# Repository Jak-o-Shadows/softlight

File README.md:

# softlight
A STM32 alarm clock that will light up a light

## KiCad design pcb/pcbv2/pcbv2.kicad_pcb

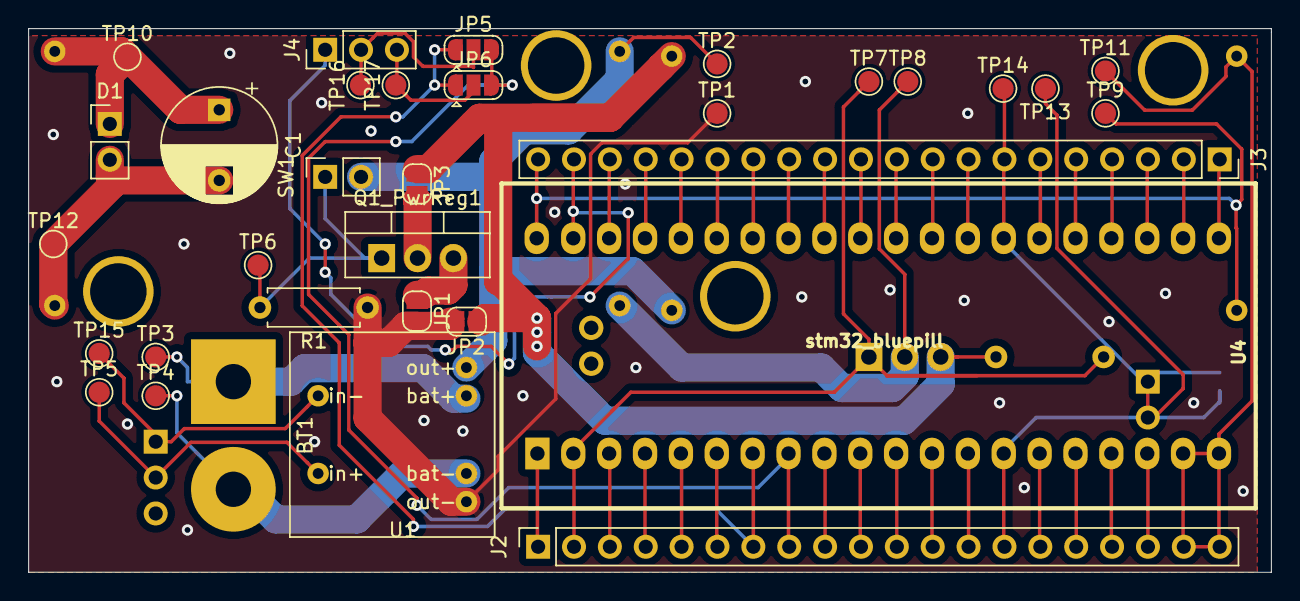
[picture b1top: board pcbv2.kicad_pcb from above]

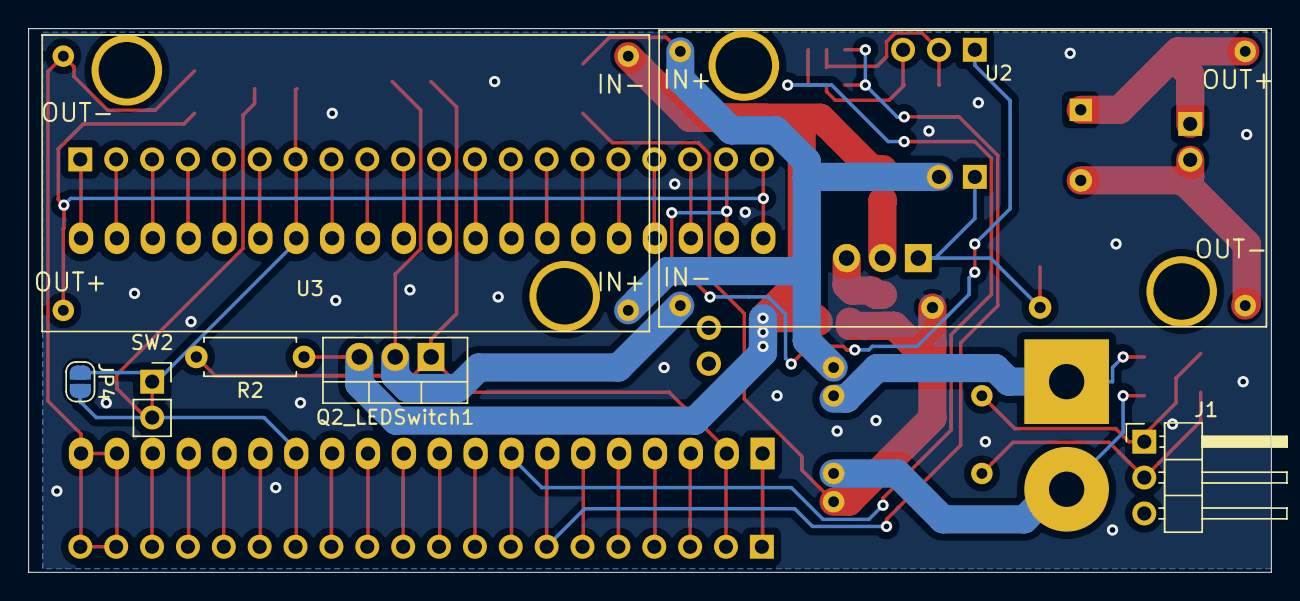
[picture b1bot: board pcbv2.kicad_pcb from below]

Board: 2 copper layers, 88.0 x 38.5 mm, 40 parts (7 on the bottom side), 54 nets.

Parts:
BT1: Battery_Cell; SolderWirePad_1x02_P7.62mm_Drill2.5mm
C1: CP; CP_Radial_D8.0mm_P5.00mm
D1: LED; PinHeader_1x02_P2.54mm_Vertical
J1: Conn_01x03_Female; PinHeader_1x03_P2.54mm_Horizontal
J2, J3: Conn_01x20_Female; PinSocket_1x20_P2.54mm_Vertical
J4: Conn_01x03_Female; PinHeader_1x03_P2.54mm_Vertical
JP1, JP2, JP3, JP4: SolderJumper_2_Open; SolderJumper-2_P1.3mm_Open_RoundedPad1.0x1.5mm
JP5, JP6: SolderJumper_3_Open; SolderJumper-3_P1.3mm_Open_RoundedPad1.0x1.5mm
Q1_PwrReg1, Q2_LEDSwitch1: IRLZ44N; TO-220-3_Vertical
R1, R2: R; R_Axial_DIN0207_L6.3mm_D2.5mm_P7.62mm_Horizontal
SW1, SW2: SW_SPST; PinSocket_1x02_P2.54mm_Vertical
TP1, TP2, TP3, TP4, TP5, TP6, TP7, TP8, TP9, TP10, TP11, TP12, TP13, TP14, TP15, TP16, TP17: TestPoint; TestPoint_Pad_D1.5mm
U1: TP4056_breakout; tp4056_breakout
U2: XL6009_Up; XL6009
U3: DSWY2596_Down; XL6009
U4: stm32_bluepill; BluePill_STM32F103C

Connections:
GND: JP1.2, JP2.2, R1.1, TP1.1, U1.6
unnamed: BT1.1, TP3.1, U1.4
unnamed: BT1.2, TP4.1, U1.5
unnamed: C1.1, D1.1, TP10.1, U2.2
unnamed: C1.2, D1.2, TP12.1, U2.3
unnamed: J1.1, TP15.1, U1.2
unnamed: J1.2, TP5.1, U1.1
unnamed: J2.1, U4.1
unnamed: J2.2, Q2_LEDSwitch1.1, R2.2, TP7.1, U4.2
unnamed: J2.3, U4.3
unnamed: J2.4, U4.4
unnamed: J2.5, U4.5
unnamed: J2.6, U4.6
unnamed: J2.7, JP5.1, JP6.1, U4.7
unnamed: J2.8, JP5.3, JP6.3, U4.8
unnamed: J2.9, U4.9
unnamed: J2.10, U4.10
unnamed: J2.11, U4.11
unnamed: J2.12, U4.12
unnamed: J2.13, U4.13
unnamed: J2.14, JP4.2, SW2.2, TP13.1, U4.14
unnamed: J2.15, U4.15
unnamed: J2.16, U4.16
unnamed: J2.17, U4.17
unnamed: J2.18, U4.18
unnamed: J2.19, J2.20, TP11.1, U3.3, U4.19, U4.20
unnamed: J3.1, U4.21
unnamed: J3.2, U4.22
unnamed: J3.3, U4.23
unnamed: J3.4, U4.24
unnamed: J3.5, U4.25
unnamed: J3.6, U4.26
unnamed: J3.7, JP4.1, SW2.1, TP14.1, U4.27
unnamed: J3.8, U4.28
unnamed: J3.9, U4.29
unnamed: J3.10, U4.30
unnamed: J3.11, U4.31
unnamed: J3.12, U4.32
unnamed: J3.13, U4.33
unnamed: J3.14, U4.34
unnamed: J3.15, U4.35
unnamed: J3.16, U4.36
unnamed: J3.17, U4.37
unnamed: J3.18, U4.38
unnamed: J3.19, J4.1, U4.39
unnamed: J3.20, TP9.1, U3.2, U4.40
unnamed: J4.2, JP5.2, TP16.1
unnamed: J4.3, JP6.2, TP17.1
unnamed: JP1.1, Q1_PwrReg1.3
unnamed: JP2.1, JP3.1, Q2_LEDSwitch1.3, R2.1, U3.5
unnamed: JP3.2, Q1_PwrReg1.2
unnamed: Q1_PwrReg1.1, R1.2, SW1.1, TP6.1
unnamed: Q2_LEDSwitch1.2, TP8.1, U2.5
unnamed: SW1.2, TP2.1, U1.3, U2.4, U3.4

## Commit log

2017-03-18 Initial setup - blinkign working
2017-03-18 Very basics of an alarm clock going
2017-05-06 Serial working! Was physically connecting it incorrectly
2017-05-07 Set the time via a desktop serial connection
2017-05-09 Serial communication working (it is byte based, not half-word), and time unscrewed
2017-05-16 Moved alarms over to structs (multiple alarms woo!) It actually works now?
2017-05-19 ACTUALLY WORKING!!!!. Also, changed motor driver wiring to allow PWM'ing it. GND -> GND, 5V -> VCC, GND->Direction (B1-A on HG7881CP), PA7->speed (B1-B on HG7881CP) (HIGH=on)
2017-05-20 USB serial - haven't connected it to configuration interface yet
2017-10-02 New format for setting time & alarms
2017-10-02 New format for setting time & alarms. Uses state machine. See 'Parsing message packets using Finite State Machine' by misterT
2017-10-28 Moved pins around - test flash of light on startup
2017-10-29 Using a timer to PWM the light. Button now has 4 modes (off, low, medium, full)
2017-11-12 Working - deployed. Swapped over to high speed external (HSE) oscillator instead of the Low speed external (LSE), as that was not working on the board when in circuit with other components. Alarms re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
2019-07-20 Working as an alarm clock, and as a torch.
    * Moved over to Python3 as well for setting time
2019-10-07 PCB - almost correct (TP4056 module not quite right size)
2019-12-27 Fix RTC presclaer (Note: Must power cycle to see impact of prescaler change). Fixed day of week alarm check.
2020-05-24 V2 PCB
2020-05-24 Changes to work with version 2 of the PCB.
2020-05-27 ¯\_(ツ)_/¯
2020-05-27 Add a print out of the current time every minute over serial (non-blocking)
2020-05-30 Fix some bugs in time I think - was having issues with going over day boundaries. * Now on time-set, sets the RTC counter to zero. On each tick, the value of the counter (not the counter!) is added t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
